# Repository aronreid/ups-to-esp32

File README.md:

# My UPS Pal 

**Put a USB-only UPS on your network. No Raspberry Pi, no SD card, no vendor network
card that costs more than the UPS.**

Plug it into the UPS's USB port and this ESP32-S3 board is a Network UPS Tools (NUT) server on TCP 3493. Home
Assistant, Synology, TrueNAS, unraid, Proxmox and `upsmon` connect to it the way they connect to
`upsd`, because that is what it is.

## Specifications

The production board, Rev B. Rev A differs in memory and fuse rating; see
[`docs/rev-a.md`](docs/rev-a.md).

| Board | |
|---|---|
| Size | 36 × 58 mm, two layers |
| Module | ESP32-S3-WROOM-1-N16R8: 16 MB flash, 8 MB PSRAM |
| Temperature | module rated to 65 °C |

| Power | |
|---|---|
| Input | 5 V over USB-C |
| Draw | about 0.08 A (0.4 W) in normal operation |
| Worst case | about 0.5 A, so any 1 A USB charger is enough |

| Ports | |
|---|---|
| UPS port | USB-A host with switched, current-limited power (1 A) |
| Computer port | USB-C for power, programming and console, with auto-reset |
| Protection | ESD protection on both USB ports and a 3 A resettable fuse |
| Lights | STATUS and FAULT LEDs |
| Display | header for an optional 0.96-inch OLED |
| Buttons | BOOT and RESET. Press BOOT five times to clear Wi-Fi and login. |

| Connectivity | |
|---|---|
| Wi-Fi | 2.4 GHz, 802.11 b/g/n |
| Setup | captive portal on `ups-esp32-XXXX` at `192.168.4.1` |
| Address | `ups-esp32-XXXX.local` over mDNS, a name you choose, or a fixed IP if you set one |
| Remote | Tailscale, built in |

| Protocols | |
|---|---|
| NUT server | TCP 3493, UPS name `ups` unless you rename it. Reads need no login. |
| UPS input | USB HID Power Device, polled |
| Metrics | Prometheus `/metrics`, names follow `nut_exporter` |
| SNMP | v2c, UPS-MIB (RFC 1628), read only, with traps. Off until you set a community. |
| Web page | live readings, battery gauge, NUT connection string and UPS controls, over HTTPS |
| NUT commands | self-test, beeper and shutdown, if your UPS supports them. Shutdown needs `OFF` typed to arm it. |

| Firmware | |
|---|---|
| Updates | over the air, signed, one click to install. Rolls back on its own if an update is bad. |
| Recovery | reconnects after a Wi-Fi drop or a UPS replug |
| History | long readings history and an outage log |
| Login | needed for setup, web changes and NUT commands |
| Build | ESP-IDF 5.5.5 |

| Enclosure | |
|---|---|
| Print | no supports. The cover snaps on, so no screws. |
| Wall mount | two countersunk holes for #6 / 3.5 mm screws, 23 mm apart |
| Details | light pipes for the LEDs and pinholes for RESET and BOOT |
| Files | STL, plus a three-colour 3MF for Bambu Studio and Orca |

---

## What it does

- **Speaks NUT.** The real protocol on port 3493. It reports what the UPS's own USB
  descriptor provides (charge, runtime, voltage, load, status) and offers only the
  controls that UPS has: self-test, beeper, shutdown. A value the UPS does not expose is
  absent, never guessed at.
- **A web page** with the readings in plain words, the UPS's controls, and the NUT
  connection string ready to paste into a client.
- **Set up in a browser.** First power raises a Wi-Fi access point; pick your network and
  the board is at `ups-esp32-XXXX.local`, or at a name you give it.
- **Updates itself**, signed, with automatic rollback if a new version does not come up.
- **Recovers on its own** from a Wi-Fi drop or a UPS that stops answering.
- **Prometheus `/metrics`**, **SNMP** with traps, and an optional OLED display.

## Works with

| Client | Configuration |
|---|---|
| **Home Assistant** | Add the built-in **NUT** integration. Usually discovered on its own; otherwise host `ups-esp32-XXXX.local`, port `3493`, UPS name `ups`, no credentials. |
| **Synology DSM** | Control Panel → Hardware & Power → UPS → *Enable UPS support*, UPS type *Synology UPS server*, and the board's IP address as the network UPS server. |
| **TrueNAS / unraid** | UPS service in "slave" or network mode, same address and port. |
| **Linux / Proxmox** | `upsmon` / `upsc ups@ups-esp32-XXXX.local` |
| **Prometheus** | Scrape `http://ups-esp32-XXXX.local/metrics` directly. Metric names follow `nut_exporter`, so its dashboards and alerts carry over. |
| **LibreNMS, PRTG, Zabbix** | Turn SNMP on under Connect on the board's Board page and set a community. Poll it as a UPS-MIB (RFC 1628) device over SNMP v2c, and give it your trap receiver's address to get on-battery, low-battery and back-on-mains traps. |

Which UPSes work: [`docs/tested-ups.md`](docs/tested-ups.md), or search the
[full compatibility list](https://myupspal.com/compatibility?utm_source=github&utm_medium=readme) by model.

---

## The boards

**Rev B** is the production board: an ESP32-S3-WROOM-1-N16R8 with the memory for
Tailscale, a long readings history, an outage log and HTTPS, on top of everything above.
Its hardware design is not published.

**Rev A** is the first board, an open-hardware design under CERN-OHL-S v2: schematic,
layout, bill of materials and printable case are in this repository, and it keeps
receiving every firmware release. See [`docs/rev-a.md`](docs/rev-a.md).

Both run the same firmware from this repository; each release carries an image for each.

Ready-made Rev B boards, with or without the OLED display, are sold at
[myupspal.com](https://myupspal.com/?utm_source=github&utm_medium=readme) and ship from Canada.

---

## Getting started

1. Download `ups-adaptor-<board>-full.bin` from [Releases](../../releases) and flash it
   over USB: `esptool.py --chip esp32s3 write_flash 0x0 ups-adaptor-revb-full.bin`
2. Join the `ups-esp32-XXXX` access point, open `http://192.168.4.1/`, choose your
   network and set the login.
3. Point your NUT client at port 3493, UPS name `ups`.

The full walk-through, including the login, a fixed address and recovery, is in
[`docs/getting-started.md`](docs/getting-started.md). Building from source:
[`firmware/README.md`](firmware/README.md). To run it on an ESP32-S3 dev board you
already have: [`docs/dev-board.md`](docs/dev-board.md).

Boards labelled "UPS to ESP32 Module" are the same product under its earlier name and
update as before.

---

## Documentation

| | |
|---|---|
| [`docs/getting-started.md`](docs/getting-started.md) | flashing, setup, the login, a fixed address, recovery |
| [`docs/tested-ups.md`](docs/tested-ups.md) | supported UPSes: verified on hardware, verified against their USB descriptors, and what cannot work |
| [`docs/updates.md`](docs/updates.md) | how a board updates, signed images, update channels |
| [`docs/firmware.md`](docs/firmware.md) | architecture, HID-to-NUT mapping, the protocol subset, the web API |
| [`firmware/README.md`](firmware/README.md) | building and flashing the firmware |
| [`docs/dev-board.md`](docs/dev-board.md) | running the firmware on a generic ESP32-S3 dev board |
| [`docs/rev-a.md`](docs/rev-a.md) | the Rev A board: photos, case, schematic, the optional display |
| [`docs/hardware.md`](docs/hardware.md) | Rev A specification, pin map, power tree, editing the design |
| [`docs/hardware-schematic.md`](docs/hardware-schematic.md) | every Rev A net and pin |
| [`docs/circuit.md`](docs/circuit.md) | the one-page circuit description |
| [`docs/BOM.md`](docs/BOM.md) | parts, and the substitutions that would break the board |
| [`docs/jlcpcb.md`](docs/jlcpcb.md) | manufacturing limits, and what to check before ordering |
| [`docs/privacy.md`](docs/privacy.md) | what the board sends, and how to turn it off |
| [`SECURITY.md`](SECURITY.md) | reporting a problem; what someone with the board in their hands can read |
| [`docs/licensing.md`](docs/licensing.md) | firmware, hardware and trademark licences |
| [`docs/CHANGELOG.md`](docs/CHANGELOG.md) | what changed in each release |

---

## Security and privacy

Updates are signed and checked by the board before they install. The login protects the
settings and controls from other devices on your network; reading the UPS never needs it.
What someone with physical access to the board can read, and what to do about it, is in
[`SECURITY.md`](SECURITY.md). What the board sends home (a short check-in, off in one
click) is in [`docs/privacy.md`](docs/privacy.md).

## Licence

Firmware: GPL-3.0-or-later. Rev A hardware: CERN-OHL-S v2. The name and logo are
trademarks and not covered by either. Details, including third-party code and how to
contribute: [`docs/licensing.md`](docs/licensing.md).

The design and direction are the author's; [Claude Code](https://claude.com/claude-code)
wrote most of the firmware and documentation under the author's review.

---

<p align="center">&nbsp; <b>Designed in Canada</b></p>

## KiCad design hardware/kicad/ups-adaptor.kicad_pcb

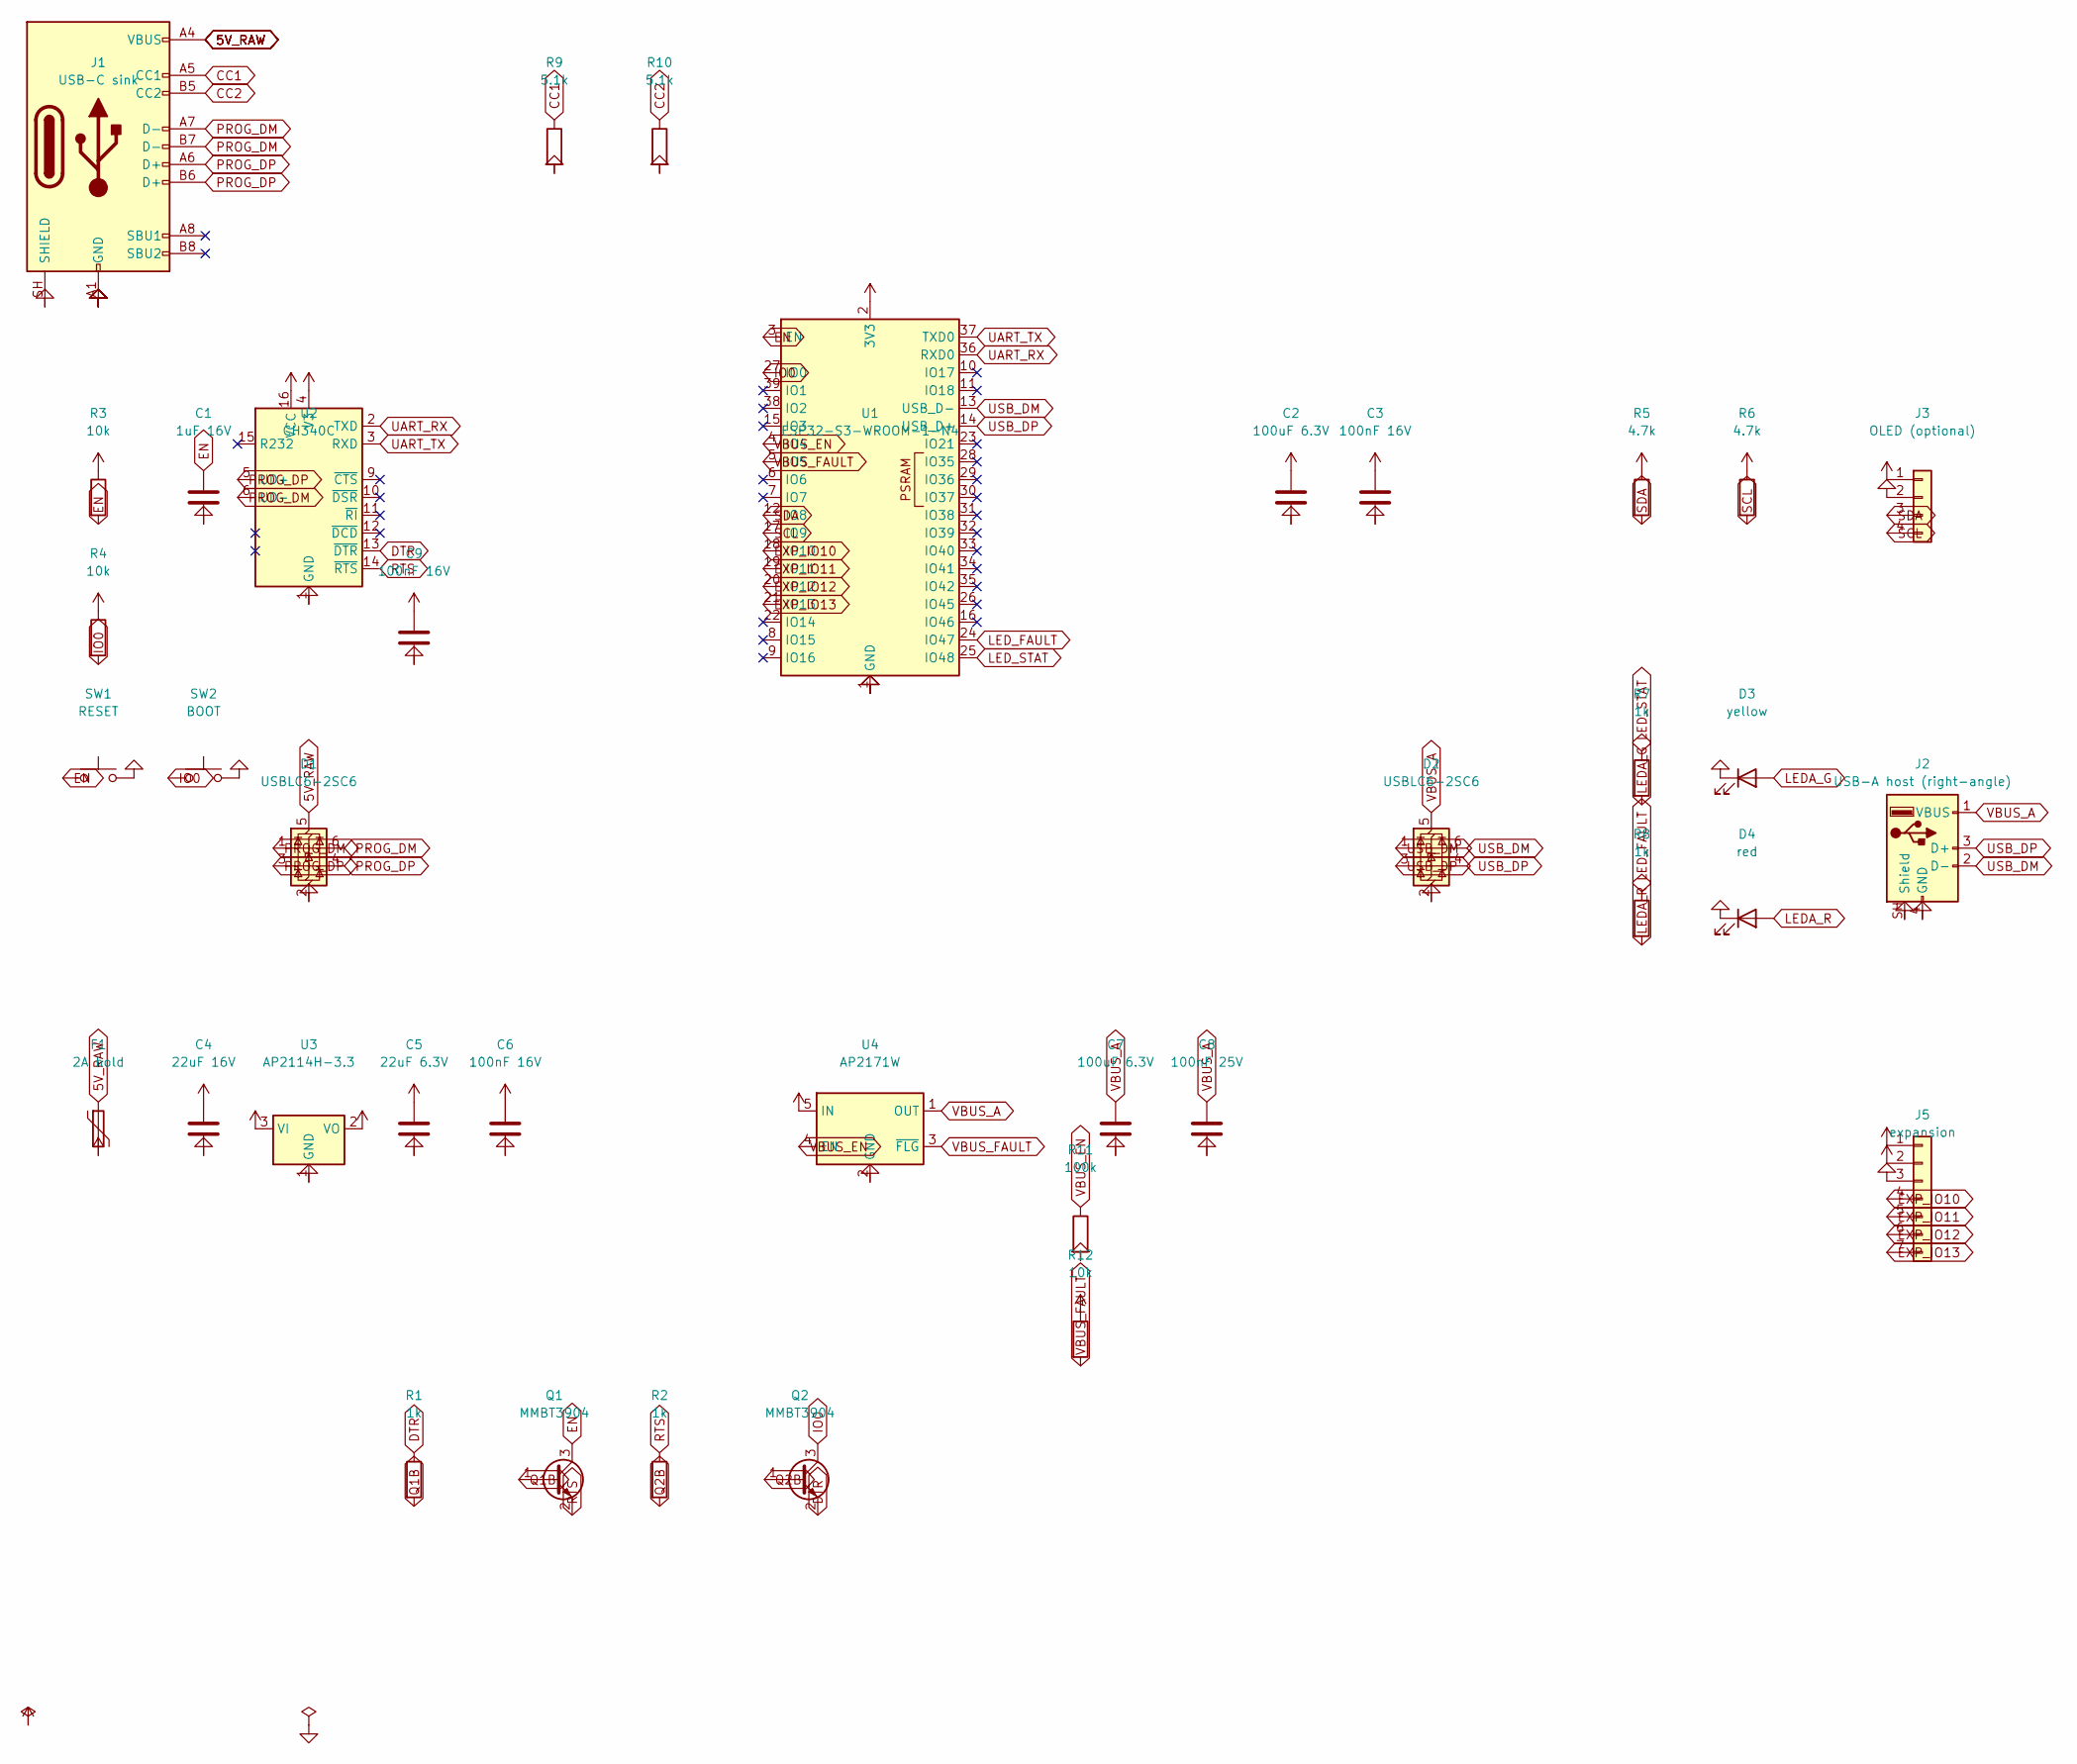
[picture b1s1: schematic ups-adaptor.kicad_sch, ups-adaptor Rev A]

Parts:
C1: 1uF 16V; C_0402_1005Metric
C2, C7: 100uF 6.3V; C_1206_3216Metric
C3, C6, C9: 100nF 16V; C_0402_1005Metric
C4: 22uF 16V; C_0805_2012Metric
C5: 22uF 6.3V; C_0805_2012Metric
C8: 100nF 25V; C_0402_1005Metric
D1, D2: USBLC6-2SC6; SOT-23-6
D3: yellow; LED_0603_1608Metric
D4: red; LED_0603_1608Metric
F1: 2A hold; Fuse_1206_3216Metric
J1: USB-C sink; USB_C_Receptacle_HRO_TYPE-C-31-M-12
J2: USB-A host (right-angle); USB_A_Receptacle_XKB_U231-091N-4BLRA00-S
J3: OLED (optional); PinSocket_1x04_P2.54mm_Vertical
J5: expansion; PinHeader_1x07_P2.54mm_Vertical
Q1, Q2: MMBT3904; SOT-23
R1, R2, R7, R8: 1k; R_0402_1005Metric
R3, R4, R12: 10k; R_0402_1005Metric
R5, R6: 4.7k; R_0402_1005Metric
R9, R10: 5.1k; R_0402_1005Metric
R11: 100k; R_0402_1005Metric
SW1: RESET; SW_Push_1P1T_XKB_TS-1187A
SW2: BOOT; SW_Push_1P1T_XKB_TS-1187A
U1: ESP32-S3-WROOM-1-N4; ESP32-S3-WROOM-1
U2: CH340C; SOIC-16_3.9x9.9mm_P1.27mm
U3: AP2114H-3.3; SOT-223-3_TabPin2
U4: AP2171W; SOT-23-5

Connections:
5V_RAW: D1.5 (VBUS), F1.1, J1.A4 (VBUS), J1.A9 (VBUS), J1.B4 (VBUS), J1.B9 (VBUS)
+3V3: C2.1, C3.1, C5.1, C6.1, C9.1, J3.1, J5.1, R3.1, R4.1, R5.1, R6.1, R12.1, U1.2 (3V3), U2.4 (V3), U2.16 (VCC), U3.2 (VO)
+5V: C4.1, F1.2, J5.2, U3.3 (VI), U4.5 (IN)
CC1: J1.A5 (CC1), R9.1
CC2: J1.B5 (CC2), R10.1
DTR: Q2.2 (E), R1.1, U2.13 (~DTR)
EN: C1.1, Q1.3 (C), R3.2, SW1.1, U1.3 (EN)
EXP_IO10: J5.4, U1.18 (IO10)
EXP_IO11: J5.5, U1.19 (IO11)
EXP_IO12: J5.6, U1.20 (IO12)
EXP_IO13: J5.7, U1.21 (IO13)
GND: C1.2, C2.2, C3.2, C4.2, C5.2, C6.2, C7.2, C8.2, C9.2, D1.2 (GND), D2.2 (GND), D3.1 (K), D4.1 (K), J1.A1 (GND), J1.A12 (GND), J1.B1 (GND), J1.B12 (GND), J1.SH (SHIELD), J2.4 (GND), J2.SH (Shield), J3.2, J5.3, R9.2, R10.2, R11.2, SW1.2, SW2.2, U1.1 (GND), U1.40 (GND), U1.41 (GND), U2.1 (GND), U3.1 (GND), U4.2 (GND)
IO0: Q2.3 (C), R4.2, SW2.1, U1.27 (IO0)
LEDA_G: D3.2 (A), R7.2
LEDA_R: D4.2 (A), R8.2
LED_FAULT: R8.1, U1.24 (IO47)
LED_STAT: R7.1, U1.25 (IO48)
PROG_DM: D1.1 (I/O1), D1.6 (I/O1), J1.A7 (D-), J1.B7 (D-), U2.6 (UD-)
PROG_DP: D1.3 (I/O2), D1.4 (I/O2), J1.A6 (D+), J1.B6 (D+), U2.5 (UD+)
Q1B: Q1.1 (B), R1.2
Q2B: Q2.1 (B), R2.2
RTS: Q1.2 (E), R2.1, U2.14 (~RTS)
SCL: J3.4, R6.2, U1.17 (IO9)
SDA: J3.3, R5.2, U1.12 (IO8)
UART_RX: U1.36 (RXD0), U2.2 (TXD)
UART_TX: U1.37 (TXD0), U2.3 (RXD)
USB_DM: D2.1 (I/O1), D2.6 (I/O1), J2.2 (D-), U1.13 (USB_D-)
USB_DP: D2.3 (I/O2), D2.4 (I/O2), J2.3 (D+), U1.14 (USB_D+)
VBUS_A: C7.1, C8.1, D2.5 (VBUS), J2.1 (VBUS), U4.1 (OUT)
VBUS_EN: R11.1, U1.4 (IO4), U4.4 (EN)
VBUS_FAULT: R12.2, U1.5 (IO5), U4.3 (~FLG)

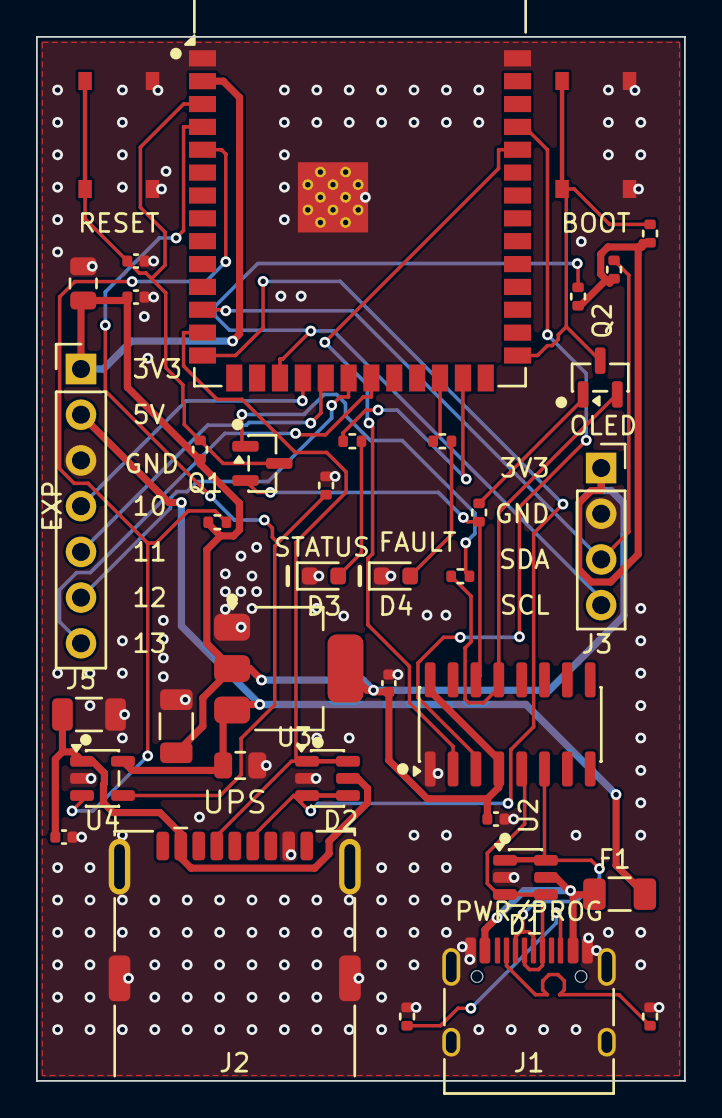
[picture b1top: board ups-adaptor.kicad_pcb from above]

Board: 2 copper layers, 36.0 x 58.0 mm, 38 parts (0 on the bottom side), 31 nets.

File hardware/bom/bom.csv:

Comment,Designator,Footprint,LCSC Part #
1uF 16V,C1,C_0402_1005Metric,C52923
100uF 6.3V,"C2,C7",C_1206_3216Metric,C15008
100nF 16V,"C3,C6,C9",C_0402_1005Metric,C1525
22uF 16V,C4,C_0805_2012Metric,C45783
22uF 6.3V,C5,C_0805_2012Metric,C45783
100nF 25V,C8,C_0402_1005Metric,C1525
USBLC6-2SC6,"D1,D2",SOT-23-6,C7519
yellow,D3,LED_0603_1608Metric,C2287
red,D4,LED_0603_1608Metric,C2286
2A hold,F1,Fuse_1206_3216Metric,C545216
USB-C sink,J1,USB_C_Receptacle_HRO_TYPE-C-31-M-12,C165948
USB-A host (right-angle),J2,USB_A_Receptacle_XKB_U231-091N-4BLRA00-S,C2880618
MMBT3904,"Q1,Q2",SOT-23,C20526
1k,"R1,R2,R7,R8",R_0402_1005Metric,C11702
10k,"R3,R4,R12",R_0402_1005Metric,C25744
4.7k,"R5,R6",R_0402_1005Metric,C25900
5.1k,"R9,R10",R_0402_1005Metric,C25905
100k,R11,R_0402_1005Metric,C25741
RESET,SW1,SW_Push_1P1T_XKB_TS-1187A,C318884
BOOT,SW2,SW_Push_1P1T_XKB_TS-1187A,C318884
ESP32-S3-WROOM-1-N4,U1,ESP32-S3-WROOM-1,C2913197
CH340C,U2,SOIC-16_3.9x9.9mm_P1.27mm,C84681
AP2114H-3.3,U3,SOT-223-3_TabPin2,C150716
AP2171W,U4,SOT-23-5,C110466

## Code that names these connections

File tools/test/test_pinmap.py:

#!/usr/bin/env python3
# SPDX-License-Identifier: GPL-3.0-or-later
"""Does the hardware match the firmware, and is every pin safe before boot?

Firmware is reflashable; copper is not. So the questions worth asking before fab
are not about features, they are:

  1. Does each BOARD_PIN_* in board.h land on the net the schematic wires?
     A pin map that disagrees with the board is a dead board, and nothing else
     in the harness compares the two.

  2. Is each pin in a defined state BEFORE firmware configures it? Every ESP32-S3
     GPIO is high-Z out of reset. Anything whose safe state depends on a level
     during that window needs a resistor, because firmware cannot act in a window
     that ends before it runs.

  3. Do the BOARD_HAS_* capability flags match what is actually fitted?
"""
import os, re, subprocess, sys, tempfile

HERE = os.path.dirname(os.path.abspath(__file__))
ROOT = os.path.dirname(os.path.dirname(HERE))
KC = "/Applications/KiCad/KiCad.app/Contents/MacOS/kicad-cli"
SYMDIR = "/Applications/KiCad/KiCad.app/Contents/SharedSupport/symbols/"
SCH = os.path.join(ROOT, "hardware", "kicad", "ups-adaptor.kicad_sch")
BOARD_H = os.path.join(ROOT, "firmware", "components", "board", "include", "board.h")

# BOARD_PIN_* -> the net that pin must be on in the schematic.
EXPECT_NET = {
    "BOARD_PIN_VBUS_EN":     "VBUS_EN",
    "BOARD_PIN_VBUS_FAULT":  "VBUS_FAULT",
    "BOARD_PIN_LED_STATUS":  "LED_STAT",
    "BOARD_PIN_LED_FAULT":   "LED_FAULT",
    "BOARD_PIN_I2C_SDA":     "SDA",
    "BOARD_PIN_I2C_SCL":     "SCL",
    "BOARD_PIN_FACTORY_BTN": "IO0",
}

# Nets whose level must be defined before firmware runs, and which way.
BOOT_STATE = [
    ("VBUS_EN", "GND", "VBUS to the UPS must be OFF until firmware asserts it; "
                       "EN is active high and GPIO4 is high-Z out of reset"),
    ("VBUS_FAULT", "+3V3", "FLG is open drain and board_vbus_fault() reads low as "
                           "a fault, so an unpulled line is a phantom fault at boot"),
    ("IO0", "+3V3", "GPIO0 is a strapping pin: low at reset means download mode"),
    ("EN", "+3V3", "the S3's reset pin must idle high"),
]

# Strapping pins that must be left unconnected.
STRAPPING_UNCONNECTED = {3: "IO3", 45: "IO45", 46: "IO46"}


def board_h_pins():
    """GPIO numbers from the Rev A branch of board.h."""
    text = open(BOARD_H).read()
    start = text.index("defined(CONFIG_UPSA_BOARD_REV_A)")
    # The branch ends at the next board (#elif) or at the no-board #else.
    end = re.compile(r"^#el(?:if|se)\b", re.M).search(text, start).start()
    body = text[start:end]
    pins, flags = {}, {}
    for m in re.finditer(r"#define\s+(BOARD_PIN_\w+)\s+GPIO_NUM_(\w+)", body):
        v = m.group(2)
        pins[m.group(1)] = None if v == "NC" else int(v)
    for m in re.finditer(r"#define\s+(BOARD_HAS_\w+)\s+(\d+)", body):
        flags[m.group(1)] = int(m.group(2))
    return pins, flags


def esp32_pin_to_gpio():
    """Map ESP32-S3-WROOM-1 symbol pin numbers to GPIO numbers."""
    txt = open(SYMDIR + "RF_Module.kicad_sym").read()
    i = txt.index('(symbol "ESP32-S3-WROOM-1"')
    depth, j = 0, i
    while j < len(txt):
        if txt[j] == "(":
            depth += 1
        elif txt[j] == ")":
            depth -= 1
            if depth == 0:
                break
        j += 1
    block = txt[i:j]
    out = {}
    for m in re.finditer(r'\(name "([^"]+)".*?\(number "([^"]+)"', block, re.S):
        nm, num = m.group(1), m.group(2)
        g = re.fullmatch(r"IO(\d+)", nm)
        if g:
            out[num] = int(g.group(1))
        elif nm == "USB_D-":
            out[num] = 19
        elif nm == "USB_D+":
            out[num] = 20
        elif nm == "TXD0":
            out[num] = 43
        elif nm == "RXD0":
            out[num] = 44
    return out


def netlist():
    tmp = tempfile.mktemp(suffix=".net")
    subprocess.run([KC, "sch", "export", "netlist", "--format", "kicadsexpr",
                    "-o", tmp, SCH], capture_output=True, text=True)
    text = open(tmp).read()
    nets = {}
    for b in re.split(r"\n\t\t\(net\n", text)[1:]:
        nm = re.search(r'\(name "([^"]+)"\)', b)
        if not nm:
            continue
        nets[nm.group(1)] = re.findall(r'\(ref "([^"]+)"\)\s*\n\s*\(pin "([^"]+)"\)', b)
    return nets


def resistor_values():
    """ref -> value, so a pull resistor can be named in the output."""
    out = {}
    for m in re.finditer(r'\(symbol\s*\n\s*\(lib_id "Device:R"\).*?'
                         r'\(property "Reference" "(R\d+)".*?\(property "Value" "([^"]+)"',
                         open(SCH).read(), re.S):
        out[m.group(1)] = m.group(2)
    return out


def main():
    pins, flags = board_h_pins()
    pin2gpio = esp32_pin_to_gpio()
    nets = netlist()
    rvals = resistor_values()
    gpio_net = {}
    for net, nodes in nets.items():
        for ref, pin in nodes:
            if ref == "U1" and pin in pin2gpio:
                gpio_net[pin2gpio[pin]] = net

    fails = 0

    # 1. firmware pin map vs schematic
    for macro, want_net in sorted(EXPECT_NET.items()):
        gpio = pins.get(macro)
        if gpio is None:
            print("  FAIL %s is NC on Rev A but the schematic expects %s" % (macro, want_net))
            fails += 1
            continue
        got = gpio_net.get(gpio)
        if got == want_net:
            print("  ok   %-22s GPIO%-2d -> %s" % (macro, gpio, got))
        else:
            print("  FAIL %-22s GPIO%-2d is on %r, firmware expects %r"
                  % (macro, gpio, got, want_net))
            fails += 1

    # 2. boot-state safety
    print()
    for net, rail, why in BOOT_STATE:
        nodes = nets.get(net, [])
        puller = None
        for ref, pin in nodes:
            if ref.startswith("R"):
                other = [n for n in nets.get(rail, []) if n[0] == ref]
                if other:
                    puller = ref
                    break
        if puller:
            print("  ok   %-11s pulled to %-5s by %s (%s)"
                  % (net, rail, puller, rvals.get(puller, "?")))
        else:
            print("  FAIL %-11s has no resistor to %s" % (net, rail))
            print("       %s" % why)
            fails += 1

    # 3. strapping pins must be unwired
    print()
    for gpio, name in sorted(STRAPPING_UNCONNECTED.items()):
        net = gpio_net.get(gpio)
        if net is None or net.startswith("unconnected-"):
            print("  ok   %-5s (GPIO%d) left unconnected" % (name, gpio))
        else:
            print("  FAIL %-5s (GPIO%d) is wired to %s -- strapping pin" % (name, gpio, net))
            fails += 1

    # 4. capability flags vs what is fitted
    print()
    has_switch = any(r == "U4" for net in nets.values() for r, _ in net)
    if bool(flags.get("BOARD_HAS_VBUS_SWITCH")) == has_switch:
        print("  ok   BOARD_HAS_VBUS_SWITCH agrees with the load switch being fitted")
    else:
        print("  FAIL BOARD_HAS_VBUS_SWITCH=%s but load switch fitted=%s"
              % (flags.get("BOARD_HAS_VBUS_SWITCH"), has_switch))
        fails += 1

    has_flag = "VBUS_FAULT" in nets
    if bool(flags.get("BOARD_HAS_VBUS_FAULT")) == has_flag:
        print("  ok   BOARD_HAS_VBUS_FAULT agrees with a fault net existing")
    else:
        print("  FAIL BOARD_HAS_VBUS_FAULT=%s but VBUS_FAULT net exists=%s"
              % (flags.get("BOARD_HAS_VBUS_FAULT"), has_flag))
        fails += 1

    return 1 if fails else 0


if __name__ == "__main__":
    sys.exit(main())

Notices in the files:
README.md:
Licence: GPL-3.0-or-later
